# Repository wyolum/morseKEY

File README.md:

# morseKEY
Morse Code USB Keyboard, from https://mitxela.com/projects/morse_code_usb_keyboard_mk_ii

Morse Key presents itself as a USB keyboard. Typing provides audible feedback via Buzzer, and morse keystrokes get typed on the computer.

## kicad

* [kicad](/kicad) - Main hardware design files. Schematic, Layout etc.

## fabricate

* [fabricate](/fabricate) - 3D CAD files / assembly files

## code

* [code](/code) - FW code

License
-------
[CERN Open Hardware Licence v1.2 ]

[CERN Open Hardware Licence v1.2 ]:http://www.ohwr.org/attachments/2388/cern_ohl_v_1_2.txt

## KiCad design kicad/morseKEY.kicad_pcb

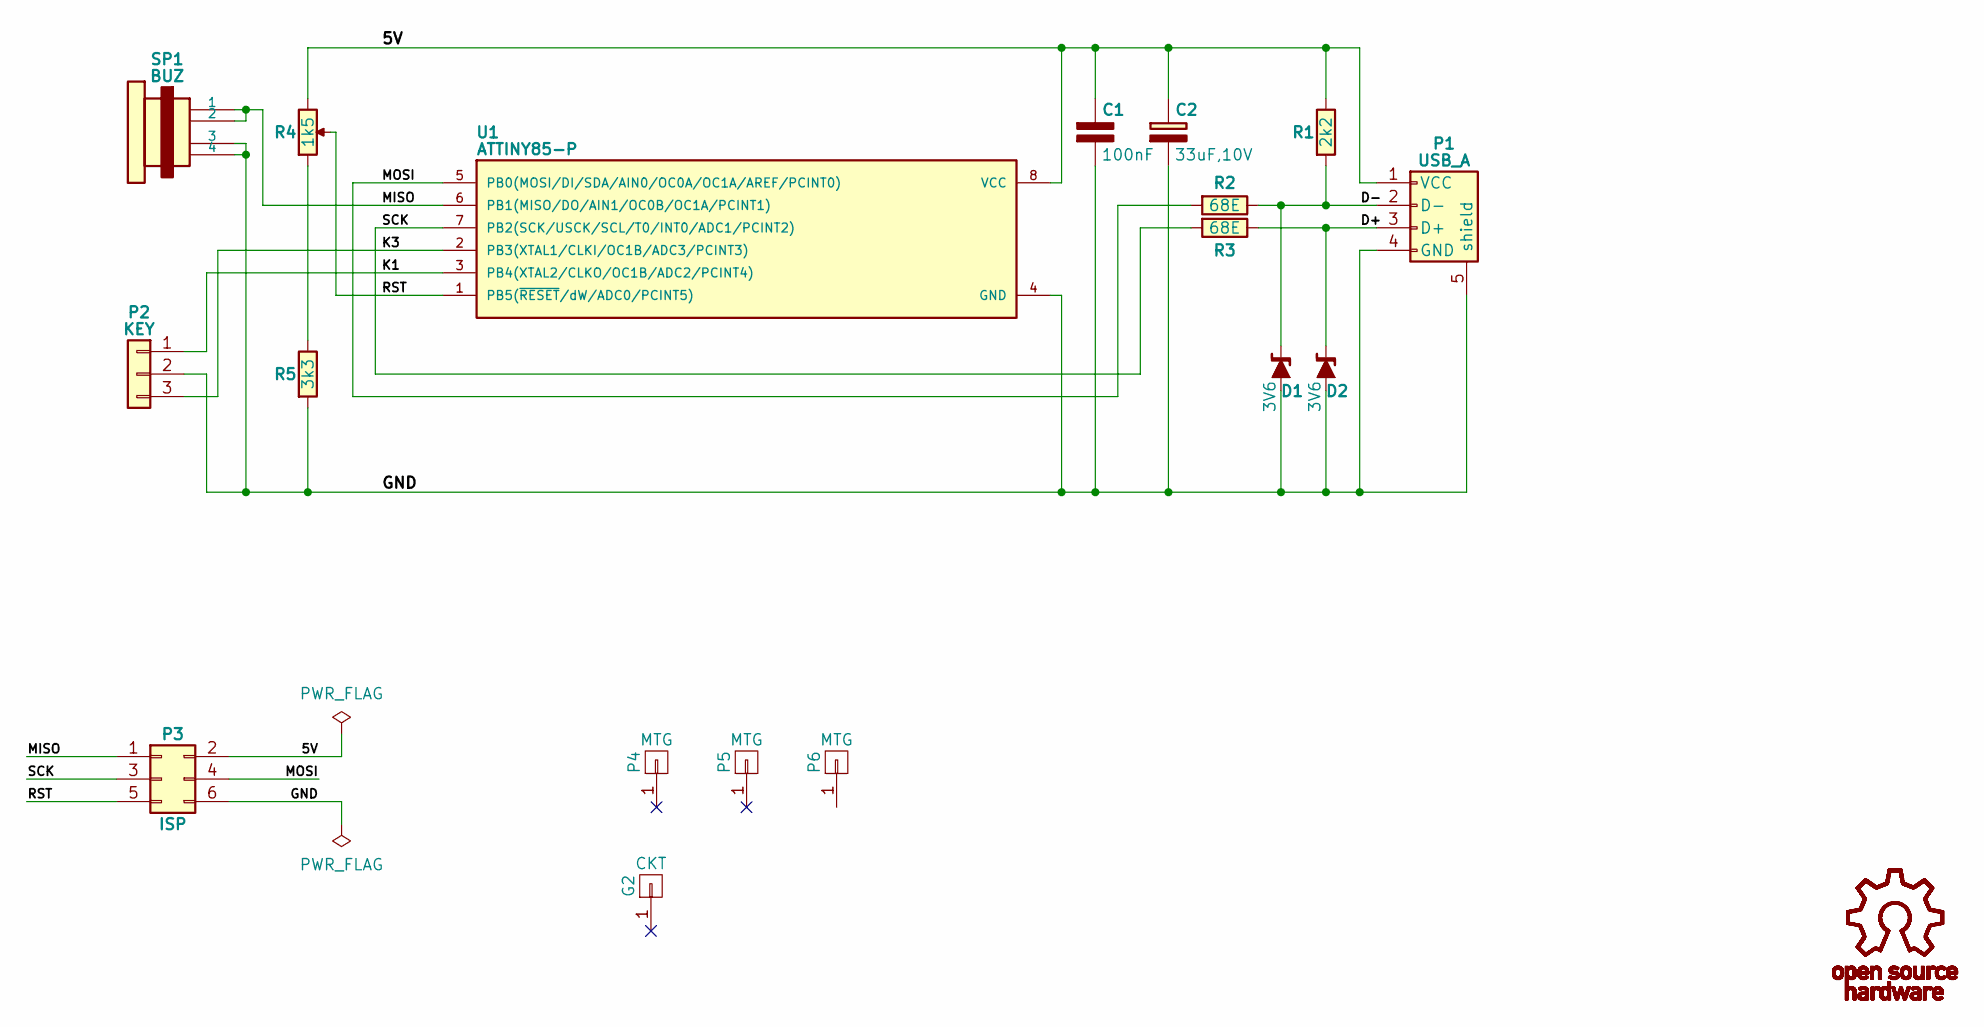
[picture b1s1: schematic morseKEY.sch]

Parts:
C1: 100nF; C_Disc_D3_P2.5
C2: 33uF,10V; C_Radial_D5_L6_P2.5
D1, D2: 3V6; Diode_DO-41_SOD81_Vertical_KathodeUp_2
G1: OSHW-LOGO; OSHW_logo_notext
G2: CKT; morseKEY
P1: USB_A; USB_A_up2-ah-th
P2: KEY; Pin_Header_Straight_1x03
P3: ISP; Pin_Header_Straight_2x03
P4, P5, P6: MTG; 1pin
R1: 2k2; Resistor_Vertical_RM5mm
R2, R3: 68E; Resistor_Vertical_RM5mm
R4: 1k5; res_vert
R5: 3k3; Resistor_Vertical_RM5mm
SP1: BUZ; Pin_Header_Straight_1x04
U1: ATTINY85-P; DIP-8_W7.62mm_LongPads

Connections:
/5V: C1.1, C2.1, P1.1 (VCC), P3.2, R1.1, R4.1, U1.8 (VCC)
/D+: D2.1 (K), P1.3 (D+), R3.1
/D-: D1.1 (K), P1.2 (D-), R1.2, R2.1
/GND: C1.2, C2.2, D1.2 (A), D2.2 (A), P1.4 (GND), P1.5 (shield), P2.2, P3.6, R5.2, SP1.3, SP1.4, U1.4 (GND)
/K1: P2.1, U1.3 (PB4(XTAL2/CLKO/OC1B/ADC2/PCINT4))
/K3: P2.3, U1.2 (PB3(XTAL1/CLKI/OC1B/ADC3/PCINT3))
/MISO: P3.1, SP1.1, SP1.2, U1.6 (PB1(MISO/DO/AIN1/OC0B/OC1A/PCINT1))
/MOSI: P3.4, R2.2, U1.5 (PB0(MOSI/DI/SDA/AIN0/OC0A/OC1A/AREF/PCI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)
/RST: P3.5, R4.2, U1.1 (PB5(~RESET~/dW/ADC0/PCINT5))
/SCK: P3.3, R3.2, U1.7 (PB2(SCK/USCK/SCL/T0/INT0/ADC1/PCINT2))
unnamed: R4.3, R5.1

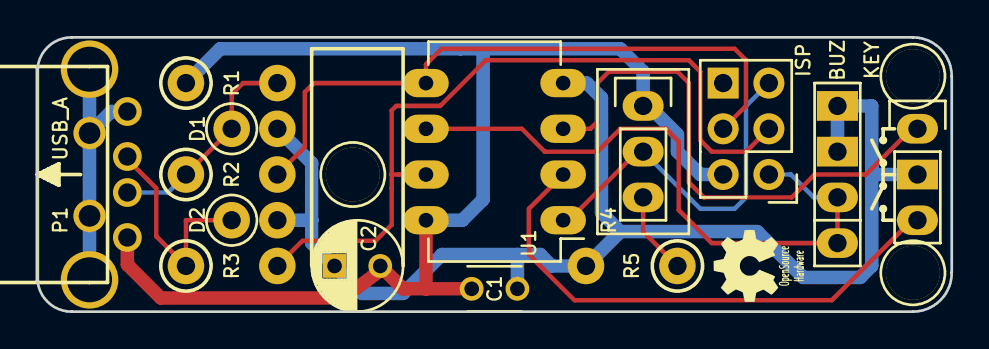
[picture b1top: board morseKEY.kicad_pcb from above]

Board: 2 copper layers, 50.8 x 15.2 mm, 18 parts (0 on the bottom side), 11 nets.

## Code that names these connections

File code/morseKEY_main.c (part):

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
/*
Pin assignment:
PB1 = waveform output to piezo
PB4 = key input (active low with pull-up)

PB0, PB2 = USB data lines
*/

#define BIT_PIEZO 1
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
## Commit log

2017-01-29 schematic
2017-01-30 board layout
2017-01-30 3D render
2017-01-31 gerbers
2017-01-31 fabricate
2017-02-01 changed RST resistor divider
2017-02-01 fixed schematic library error
2017-06-09 added full source code and updated makefile for morseKey firmware
2017-06-21 reverse pinout of USB connector, reroute
2017-06-21 update gerbers
2020-04-16 morseKEY update for KiCad FreeCAD demo tutorial
